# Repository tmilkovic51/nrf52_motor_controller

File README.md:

# NRF52 motor controller devkit
A PCB integrating the nRF52832 MCU and DRV8876 motor controller with low power considerations, designed in KiCad.

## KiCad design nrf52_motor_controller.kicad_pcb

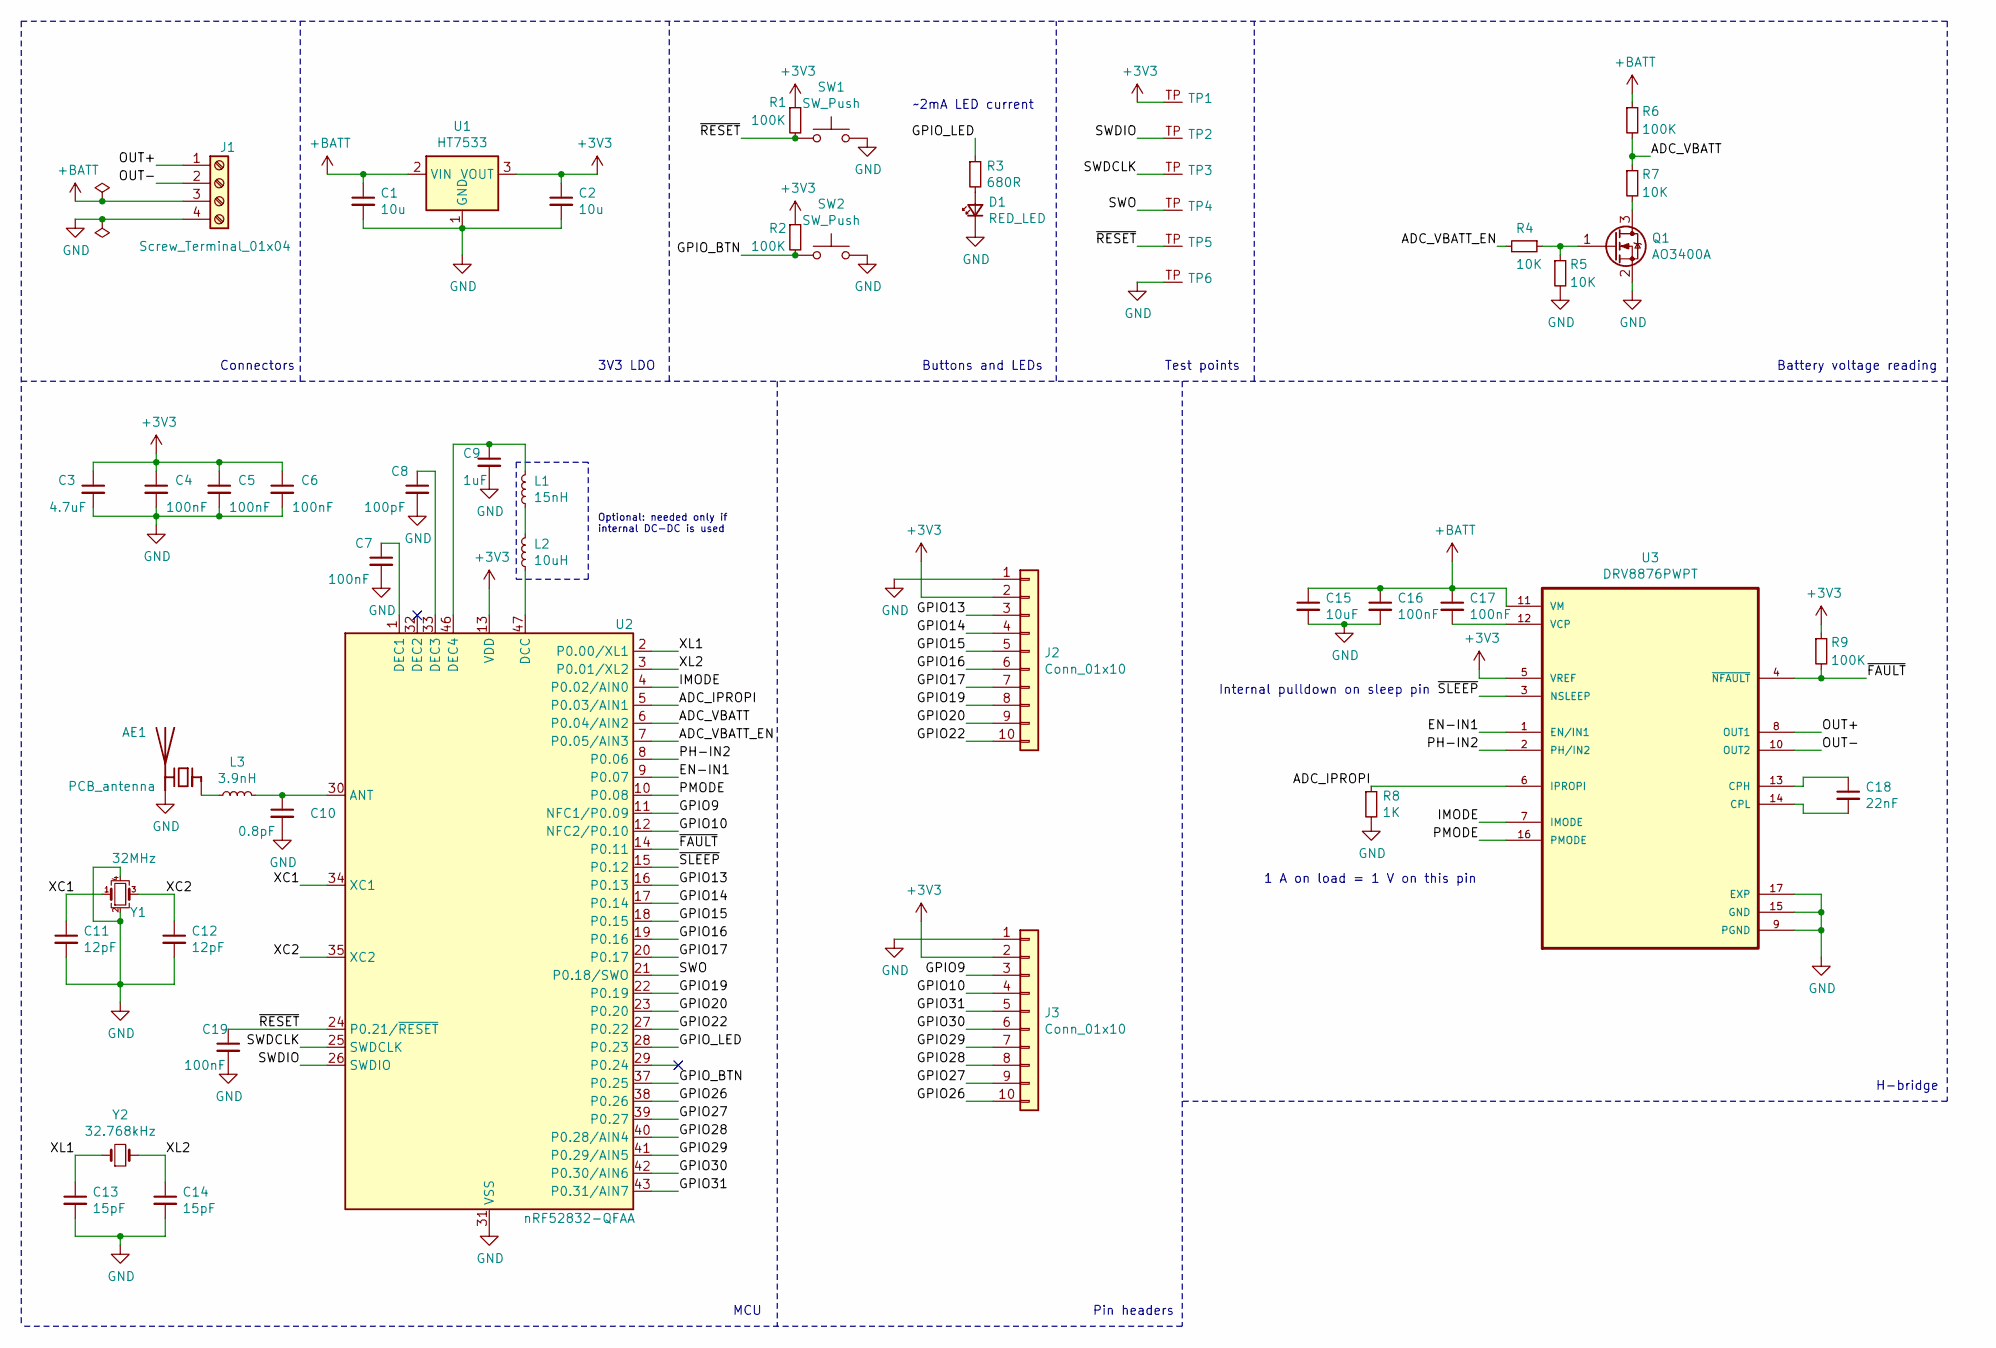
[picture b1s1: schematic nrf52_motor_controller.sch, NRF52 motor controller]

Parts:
AE1: PCB_antenna; Texas_SWRA117D_2.4GHz_Left
C1, C2: 10u; C_0603_1608Metric
C3: 4.7uF; C_0603_1608Metric
C4, C5, C6, C7, C16, C17, C19: 100nF; C_0402_1005Metric
C8: 100pF; C_0402_1005Metric
C9: 1uF; C_0603_1608Metric
C10: 0.8pF; C_0402_1005Metric
C11, C12: 12pF; C_0402_1005Metric
C13, C14: 15pF; C_0402_1005Metric
C15: 10uF; C_0805_2012Metric
C18: 22nF; C_0402_1005Metric
D1: RED_LED; LED_0603_1608Metric
J1: Screw_Terminal_01x04; TerminalBlock_Phoenix_MKDS-1,5-4_1x04_P5.00mm_Horizontal
J2, J3: Conn_01x10; PinHeader_1x10_P2.54mm_Vertical
L1: 15nH; L_0402_1005Metric
L2: 10uH; L_0603_1608Metric
L3: 3.9nH; L_0402_1005Metric
Q1: AO3400A; SOT-23; LCSC C20917
R1, R2: 100K; R_0402_1005Metric; LCSC C23228
R3: 680R; R_0603_1608Metric; LCSC C23228
R4, R5, R7: 10K; R_0402_1005Metric
R6, R9: 100K; R_0402_1005Metric
R8: 1K; R_0603_1608Metric
SW1, SW2: SW_Push; SW_SPST_CK_RS282G05A3
TP1, TP2, TP3, TP4, TP5, TP6: Test_point_1mm; test_point_1mm
U1: HT7533; SOT-89-3; LCSC C14289
U2: nRF52832-QFAA; QFN-48-1EP_6x6mm_P0.4mm_EP4.6x4.6mm; LCSC C77540
U3: DRV8876PWPT; HTSSOP-16-1EP_4.4x5mm_P0.65mm_EP3.4x5mm_Mask3x3mm_ThermalVi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; PARTREV E; LCSC C575551
Y1: 32MHz; Crystal_SMD_2016-4Pin_2.0x1.6mm; LCSC C843260
Y2: 32.768kHz; Crystal_SMD_3215-2Pin_3.2x1.5mm; LCSC C32346

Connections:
+3V3: C2.1, C3.1, C4.1, C5.1, C6.1, J2.2, J3.2, R1.1, R2.1, R9.1, TP1.TP, U1.3 (VOUT), U2.13 (VDD), U2.36 (VDD), U2.48 (VDD), U3.5 (VREF)
+BATT: C1.1, C15.1, C16.1, C17.1, J1.3, R6.1, U1.2 (VIN), U3.11 (VM)
/ADC_IPROPI: R8.1, U2.5 (P0.03/AIN1), U3.6 (IPROPI)
/ADC_VBATT: R6.2, R7.1, U2.6 (P0.04/AIN2)
/ADC_VBATT_EN: R4.2, U2.7 (P0.05/AIN3)
/EN-IN1: U2.9 (P0.07), U3.1 (EN/IN1)
/GPIO9: J3.3, U2.11 (NFC1/P0.09)
/GPIO10: J3.4, U2.12 (NFC2/P0.10)
/GPIO13: J2.3, U2.16 (P0.13)
/GPIO14: J2.4, U2.17 (P0.14)
/GPIO15: J2.5, U2.18 (P0.15)
/GPIO16: J2.6, U2.19 (P0.16)
/GPIO17: J2.7, U2.20 (P0.17)
/GPIO19: J2.8, U2.22 (P0.19)
/GPIO20: J2.9, U2.23 (P0.20)
/GPIO22: J2.10, U2.27 (P0.22)
/GPIO26: J3.10, U2.38 (P0.26)
/GPIO27: J3.9, U2.39 (P0.27)
/GPIO28: J3.8, U2.40 (P0.28/AIN4)
/GPIO29: J3.7, U2.41 (P0.29/AIN5)
/GPIO30: J3.6, U2.42 (P0.30/AIN6)
/GPIO31: J3.5, U2.43 (P0.31/AIN7)
/GPIO_BTN: R2.2, SW2.1, U2.37 (P0.25)
/GPIO_LED: R3.1, U2.28 (P0.23)
/IMODE: U2.4 (P0.02/AIN0), U3.7 (IMODE)
/OUT+: J1.1, U3.8 (OUT1)
/OUT-: J1.2, U3.10 (OUT2)
/PH-IN2: U2.8 (P0.06), U3.2 (PH/IN2)
/PMODE: U2.10 (P0.08), U3.16 (PMODE)
/SWDCLK: TP3.TP, U2.25 (SWDCLK)
/SWDIO: TP2.TP, U2.26 (SWDIO)
/SWO: TP4.TP, U2.21 (P0.18/SWO)
/XC1: C11.1, U2.34 (XC1), Y1.1
/XC2: C12.1, U2.35 (XC2), Y1.3
/XL1: C13.1, U2.2 (P0.00/XL1), Y2.1
/XL2: C14.1, U2.3 (P0.01/XL2), Y2.2
/~FAULT: R9.2, U2.14 (P0.11), U3.4 (~NFAULT)
/~RESET: C19.1, R1.2, SW1.1, TP5.TP, U2.24 (P0.21/~RESET)
/~SLEEP: U2.15 (P0.12), U3.3 (NSLEEP)
GND: AE1.2 (PCB_Trace), C1.2, C2.2, C3.2, C4.2, C5.2, C6.2, C7.2, C8.2, C9.2, C10.2, C11.2, C12.2, C13.2, C14.2, C15.2, C16.2, C19.2, D1.1 (K), J1.4, J2.1, J3.1, Q1.2 (S), R5.2, R8.2, SW1.2, SW2.2, TP6.TP, U1.1 (GND), U2.31 (VSS), U2.45 (VSS), U2.49 (VSS), U3.9 (PGND), U3.15 (GND), U3.17 (EXP), Y1.2, Y1.4
unnamed: AE1.1 (FEED), L3.1
unnamed: C7.1, U2.1 (DEC1)
unnamed: C8.1, U2.33 (DEC3)
unnamed: C9.1, L1.2, U2.46 (DEC4)
unnamed: C10.1, L3.2, U2.30 (ANT)
unnamed: C17.2, U3.12 (VCP)
unnamed: C18.1, U3.13 (CPH)
unnamed: C18.2, U3.14 (CPL)
unnamed: D1.2 (A), R3.2
unnamed: L1.1, L2.2
unnamed: L2.1, U2.47 (DCC)
unnamed: Q1.1 (G), R4.1, R5.1
unnamed: Q1.3 (D), R7.2

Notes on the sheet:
Connectors
3V3 LDO
1 A on load = 1 V on this pin
Internal pulldown on sleep pin
Buttons and LEDs
Test points
MCU
H-bridge
Pin headers
Battery voltage reading
~~2mA LED current
Optional: needed only if internal DC-DC is used

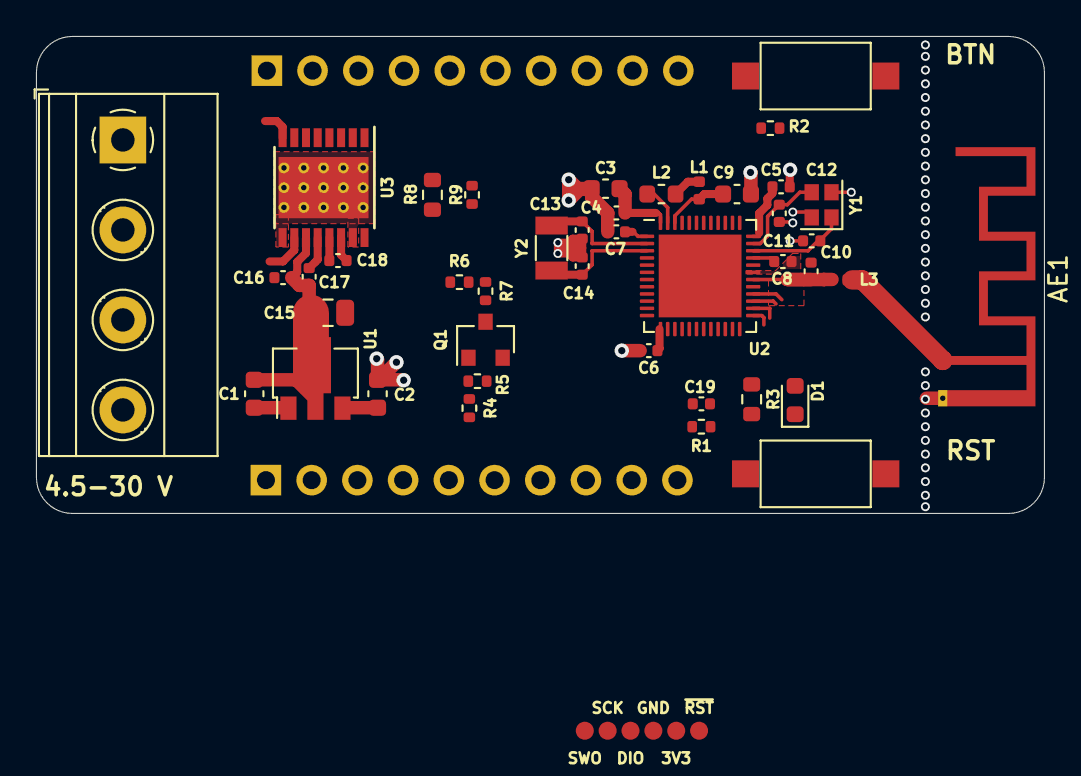
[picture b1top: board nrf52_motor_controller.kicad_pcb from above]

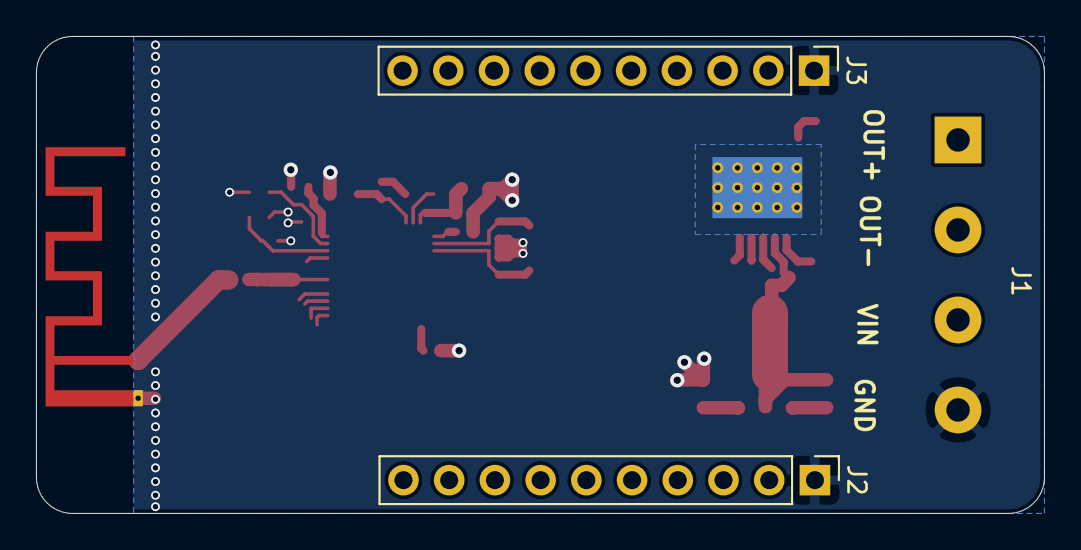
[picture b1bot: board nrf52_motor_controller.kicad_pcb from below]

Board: 2 copper layers, 56.0 x 26.5 mm, 50 parts (2 on the bottom side), 53 nets.

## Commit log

2023-01-07 Initial commit
    Add necessary libraries
    Design initial version of schematic
    Design initial version of PCB
2023-01-07 Replace 12 pin headers with 10 pin
2023-02-01 Add custom test point symbol and footprint for 1.27 mm pitch TP

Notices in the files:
nrf52_motor_controller.sch:
Copyright: Tomislav Milkovic
